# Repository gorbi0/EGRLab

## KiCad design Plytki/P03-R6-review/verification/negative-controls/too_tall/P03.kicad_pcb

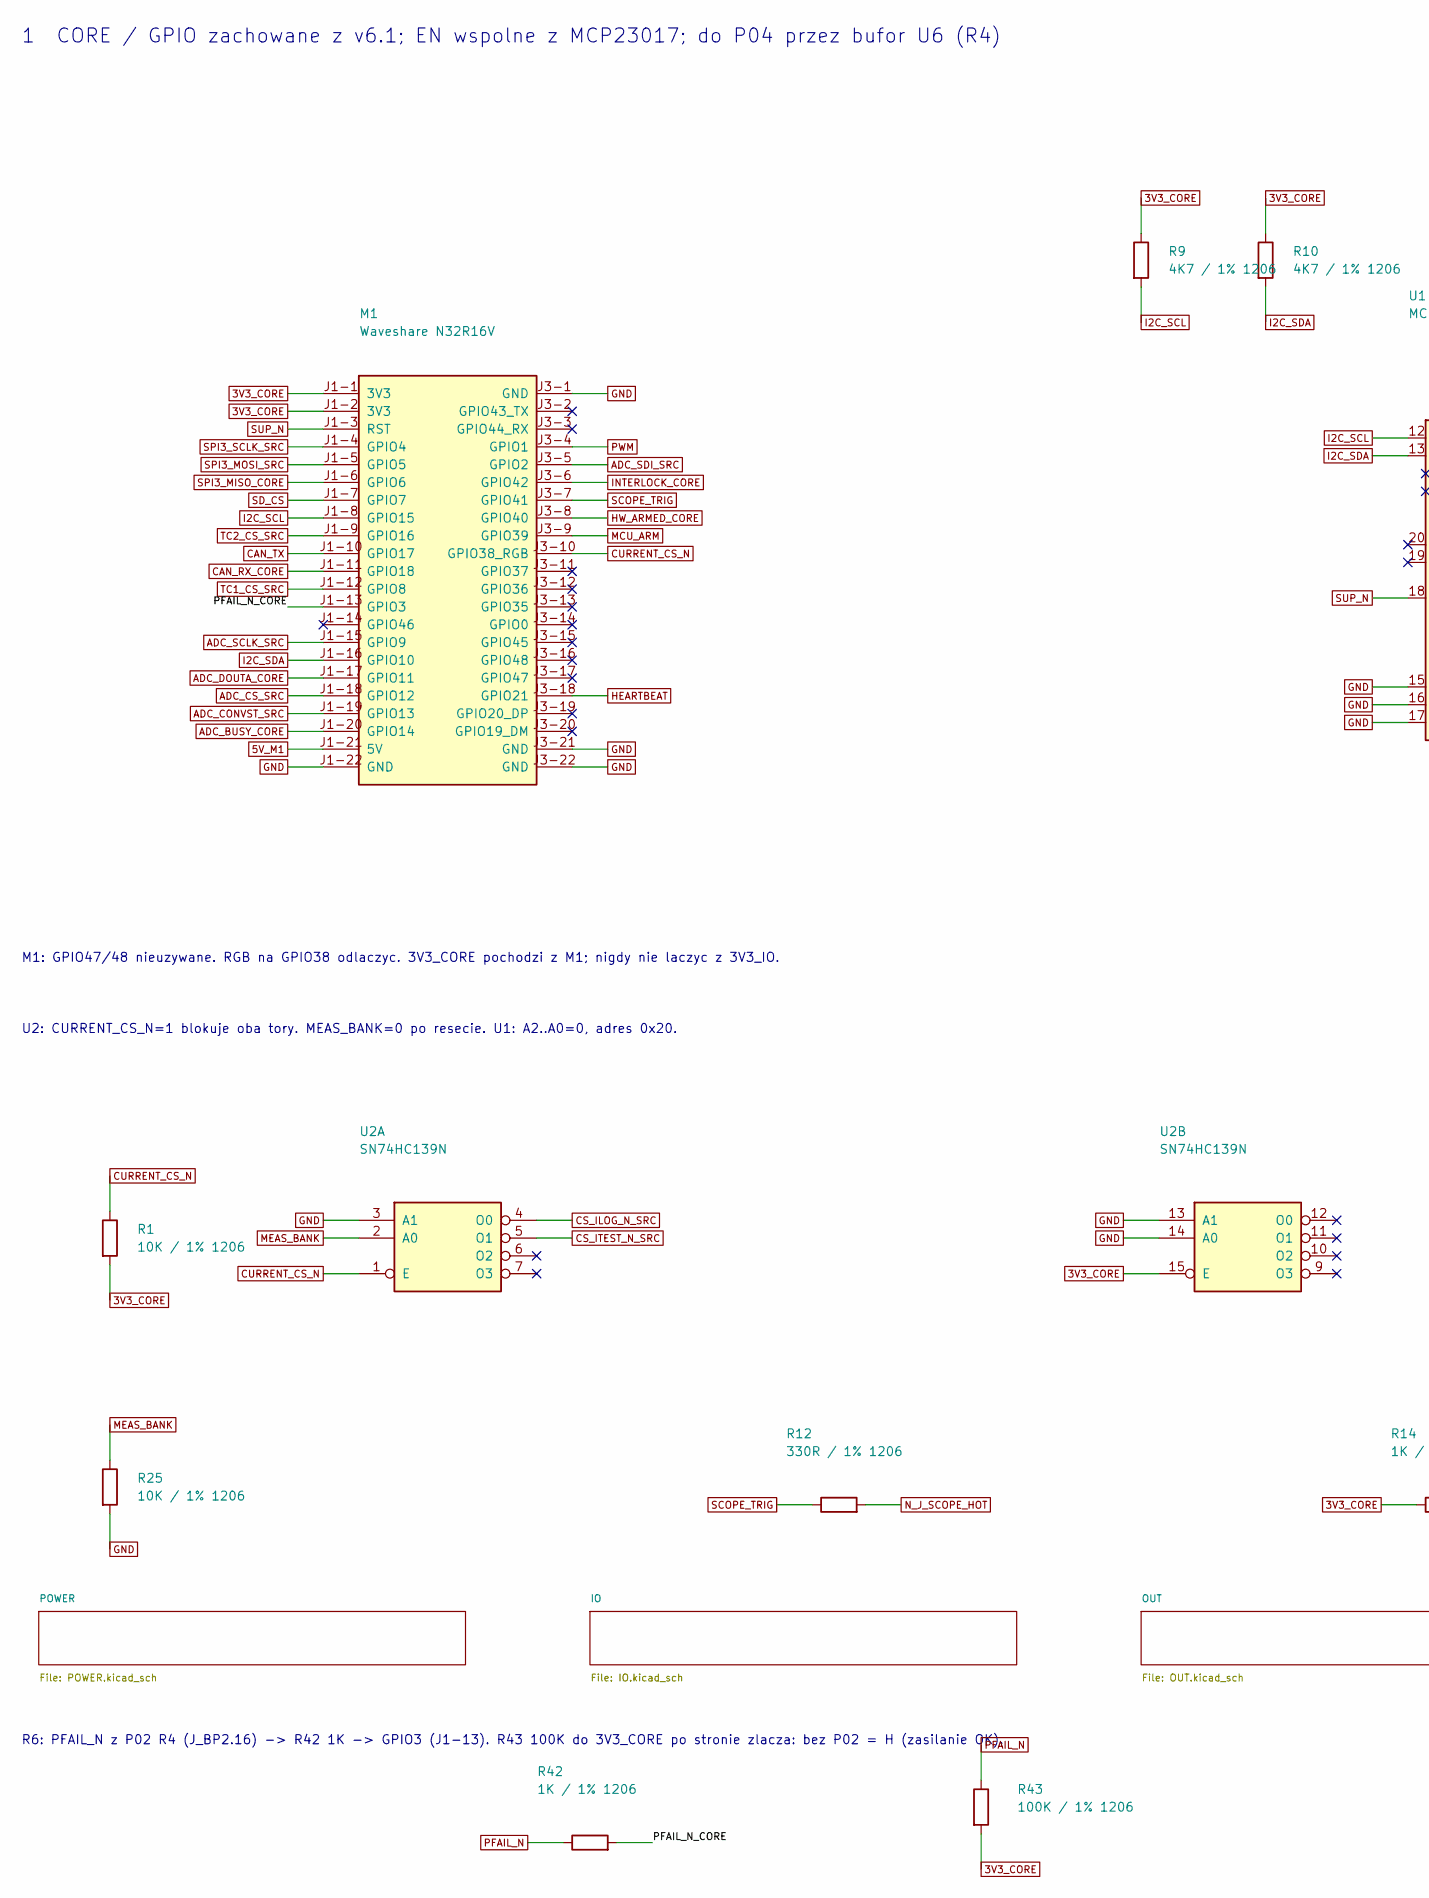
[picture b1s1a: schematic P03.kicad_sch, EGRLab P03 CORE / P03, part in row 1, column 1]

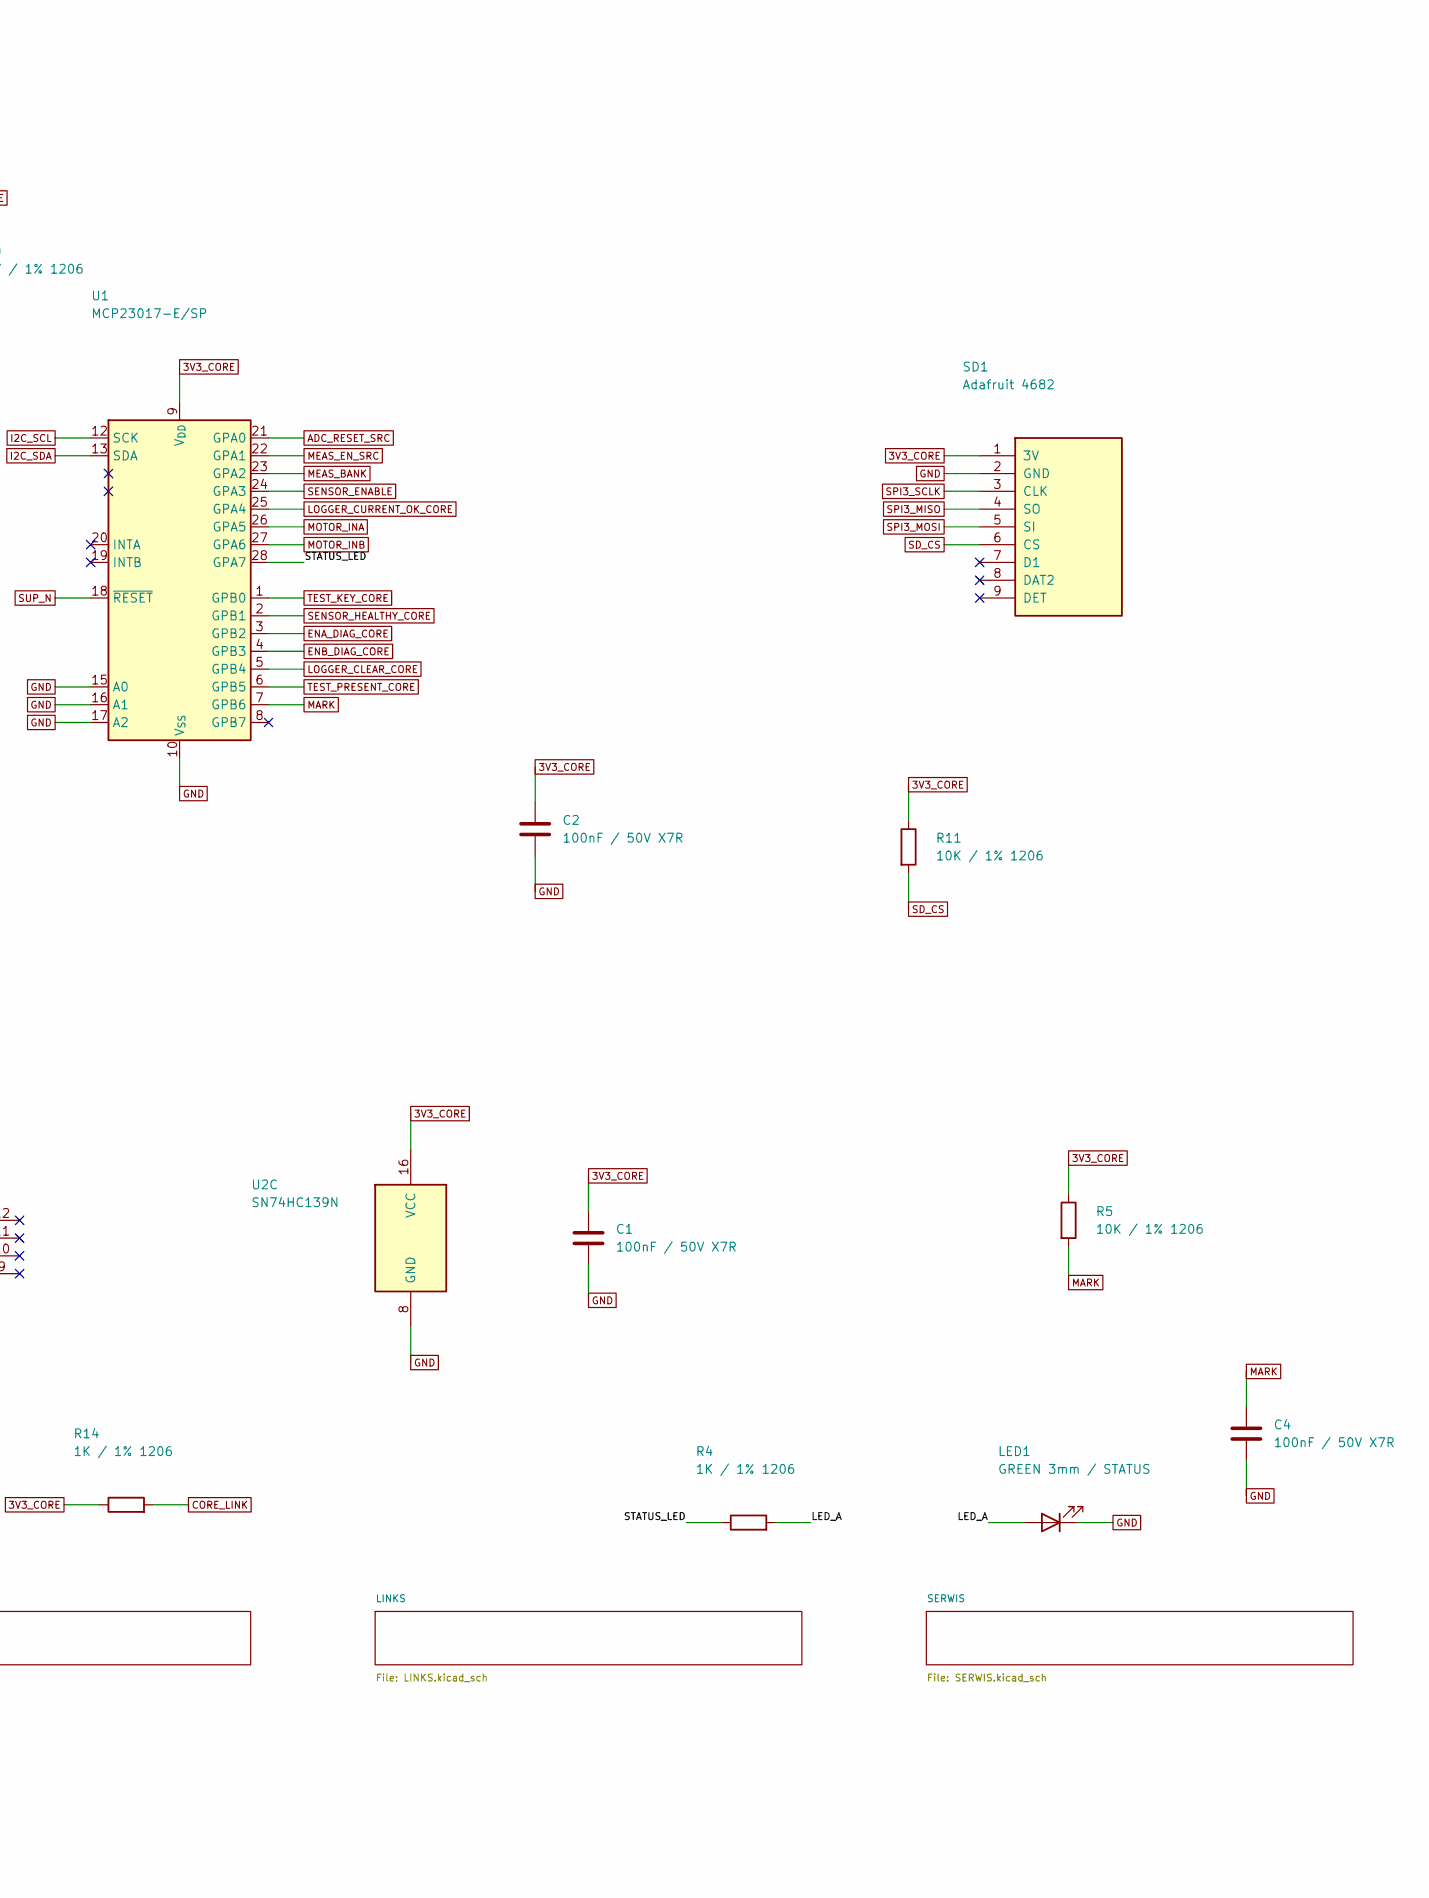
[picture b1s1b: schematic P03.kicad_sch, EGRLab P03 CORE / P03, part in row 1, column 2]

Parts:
C1, C2, C4: 100nF / 50V X7R; C_1206_3216Metric_Pad1.33x1.80mm_HandSolder; MPN GRM31CR71H104KA01L
LED1: GREEN 3mm / STATUS; LED_D3.0mm; MPN L-934GD
M1: Waveshare N32R16V; Waveshare_ESP32-S3-DEV-KIT_2x22_W22.86; MPN owned (Waveshare ESP32-S3-DEV-KIT-N32R1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
R1, R5, R11, R25: 10K / 1% 1206; R_1206_3216Metric_Pad1.30x1.75mm_HandSolder; MPN RC1206FR-0710KL
R4, R14, R42: 1K / 1% 1206; R_1206_3216Metric_Pad1.30x1.75mm_HandSolder; MPN RC1206FR-071KL
R9, R10: 4K7 / 1% 1206; R_1206_3216Metric_Pad1.30x1.75mm_HandSolder; MPN RC1206FR-074K7L
R12: 330R / 1% 1206; R_1206_3216Metric_Pad1.30x1.75mm_HandSolder; MPN RC1206FR-07330RL
R43: 100K / 1% 1206; R_1206_3216Metric_Pad1.30x1.75mm_HandSolder; MPN RC1206FR-07100KL
SD1: Adafruit 4682; Adafruit_4682_microSD_1x09; MPN Adafruit 4682 on a 1x9 female header + 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
U1: MCP23017-E/SP; DIP-28_W7.62mm; MPN MCP23017-E/SP
U2: SN74HC139N; DIP-16_W7.62mm; MPN SN74HC139N

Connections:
5V_M1: M1.J1-21 (5V); also elsewhere on the board
/LED_A: LED1.2 (A), R4.2
/PFAIL_N_CORE: M1.J1-13 (GPIO3), R42.2
/STATUS_LED: R4.1, U1.28 (GPA7)
ADC_BUSY_CORE: M1.J1-20 (GPIO14); also elsewhere on the board
ADC_CONVST_SRC: M1.J1-19 (GPIO13); also elsewhere on the board
ADC_CS_SRC: M1.J1-18 (GPIO12); also elsewhere on the board
ADC_DOUTA_CORE: M1.J1-17 (GPIO11); also elsewhere on the board
ADC_RESET_SRC: U1.21 (GPA0); also elsewhere on the board
ADC_SCLK_SRC: M1.J1-15 (GPIO9); also elsewhere on the board
ADC_SDI_SRC: M1.J3-5 (GPIO2); also elsewhere on the board
CAN_RX_CORE: M1.J1-11 (GPIO18); also elsewhere on the board
CAN_TX: M1.J1-10 (GPIO17); also elsewhere on the board
CORE_LINK: R14.2; also elsewhere on the board
CS_ILOG_N_SRC: U2.4 (O0); also elsewhere on the board
CS_ITEST_N_SRC: U2.5 (O1); also elsewhere on the board
ENA_DIAG_CORE: U1.3 (GPB2); also elsewhere on the board
ENB_DIAG_CORE: U1.4 (GPB3); also elsewhere on the board
GND: C1.2, C2.2, C4.2, LED1.1 (K), M1.J1-22 (GND), M1.J3-1 (GND), M1.J3-21 (GND), M1.J3-22 (GND), R25.2, SD1.2 (GND), U1.10 (V_{SS}), U1.15 (A0), U1.16 (A1), U1.17 (A2), U2.3 (A1), U2.8 (GND), U2.13 (A1), U2.14 (A0); also elsewhere on the board
HEARTBEAT: M1.J3-18 (GPIO21); also elsewhere on the board
HW_ARMED_CORE: M1.J3-8 (GPIO40); also elsewhere on the board
I2C_SDA: M1.J1-16 (GPIO10), R10.2, U1.13 (SDA); also elsewhere on the board
INTERLOCK_CORE: M1.J3-6 (GPIO42); also elsewhere on the board
LOGGER_CLEAR_CORE: U1.5 (GPB4); also elsewhere on the board
LOGGER_CURRENT_OK_CORE: U1.25 (GPA4); also elsewhere on the board
MARK: C4.1, R5.2, U1.7 (GPB6); also elsewhere on the board
MCU_ARM: M1.J3-9 (GPIO39); also elsewhere on the board
MEAS_EN_SRC: U1.22 (GPA1); also elsewhere on the board
MOTOR_INA: U1.26 (GPA5); also elsewhere on the board
MOTOR_INB: U1.27 (GPA6); also elsewhere on the board
N_J_SCOPE_HOT: R12.2; also elsewhere on the board
PWM: M1.J3-4 (GPIO1); also elsewhere on the board
SCOPE_TRIG: M1.J3-7 (GPIO41), R12.1; also elsewhere on the board
SD_CS: M1.J1-7 (GPIO7), R11.2, SD1.6 (CS); also elsewhere on the board
SENSOR_ENABLE: U1.24 (GPA3); also elsewhere on the board
SENSOR_HEALTHY_CORE: U1.2 (GPB1); also elsewhere on the board
SPI3_MISO: SD1.4 (SO); also elsewhere on the board
SPI3_MISO_CORE: M1.J1-6 (GPIO6); also elsewhere on the board
SPI3_MOSI: SD1.5 (SI); also elsewhere on the board
SPI3_MOSI_SRC: M1.J1-5 (GPIO5); also elsewhere on the board
SPI3_SCLK: SD1.3 (CLK); also elsewhere on the board
SPI3_SCLK_SRC: M1.J1-4 (GPIO4); also elsewhere on the board
SUP_N: M1.J1-3 (RST), U1.18 (~RESET); also elsewhere on the board
TC1_CS_SRC: M1.J1-12 (GPIO8); also elsewhere on the board
TC2_CS_SRC: M1.J1-9 (GPIO16); also elsewhere on the board
TEST_KEY_CORE: U1.1 (GPB0); also elsewhere on the board
TEST_PRESENT_CORE: U1.6 (GPB5); also elsewhere on the board

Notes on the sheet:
1 CORE / GPIO zachowane z v6.1; EN wspolne z MCP23017; do P04 przez bufor U6 (R4)
M1: GPIO47/48 nieuzywane. RGB na GPIO38 odlaczyc. 3V3_CORE pochodzi z M1; nigdy nie laczyc z 3V3_IO.
U2: CURRENT_CS_N=1 blokuje oba tory. MEAS_BANK=0 po resecie. U1: A2..A0=0, adres 0x20.
R6: PFAIL_N z P02 R4 (J_BP2.16) -> R42 1K -> GPIO3 (J1-13). R43 100K do 3V3_CORE po stronie zlacza: bez P02 = H (zasilanie OK).

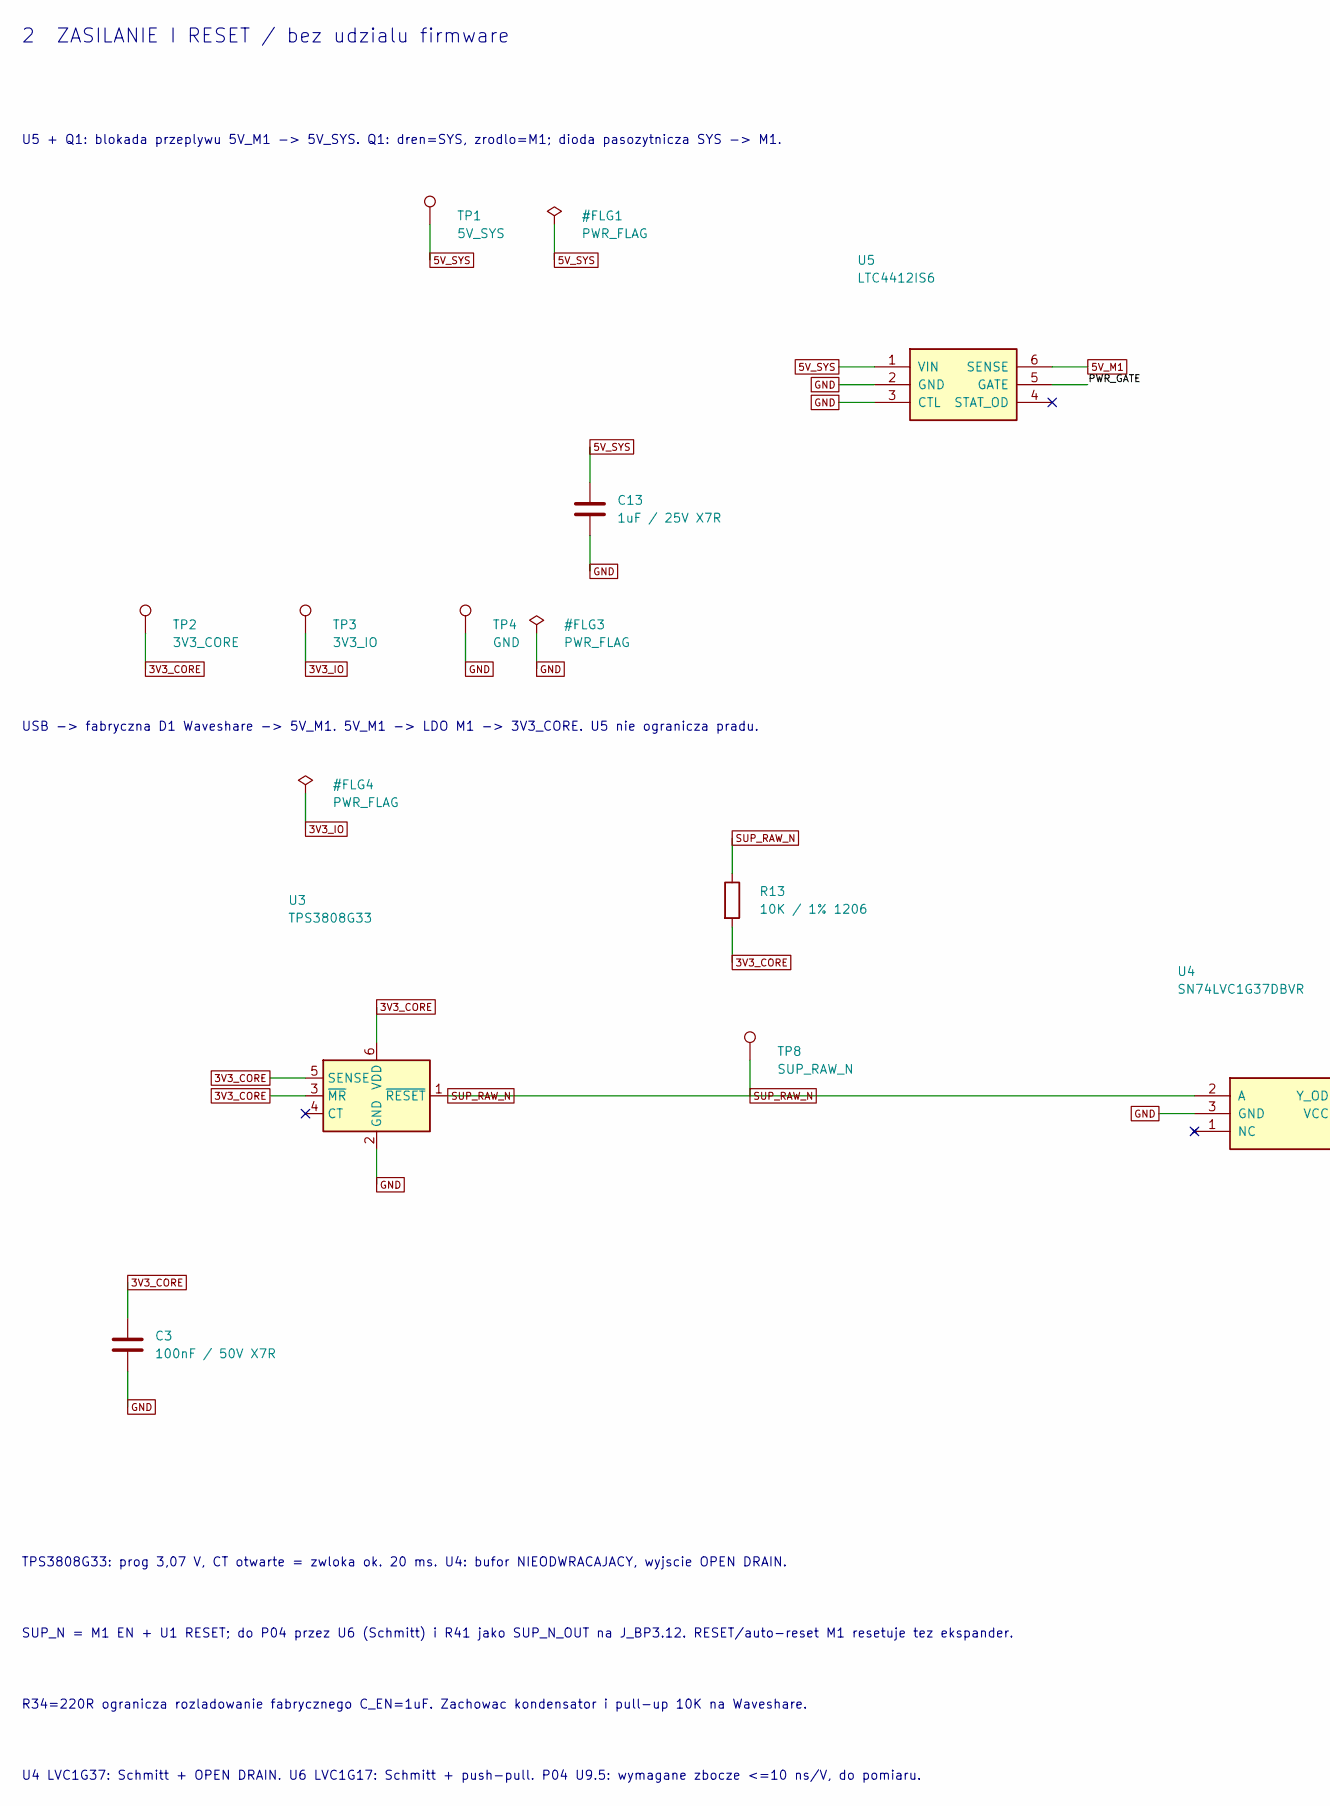
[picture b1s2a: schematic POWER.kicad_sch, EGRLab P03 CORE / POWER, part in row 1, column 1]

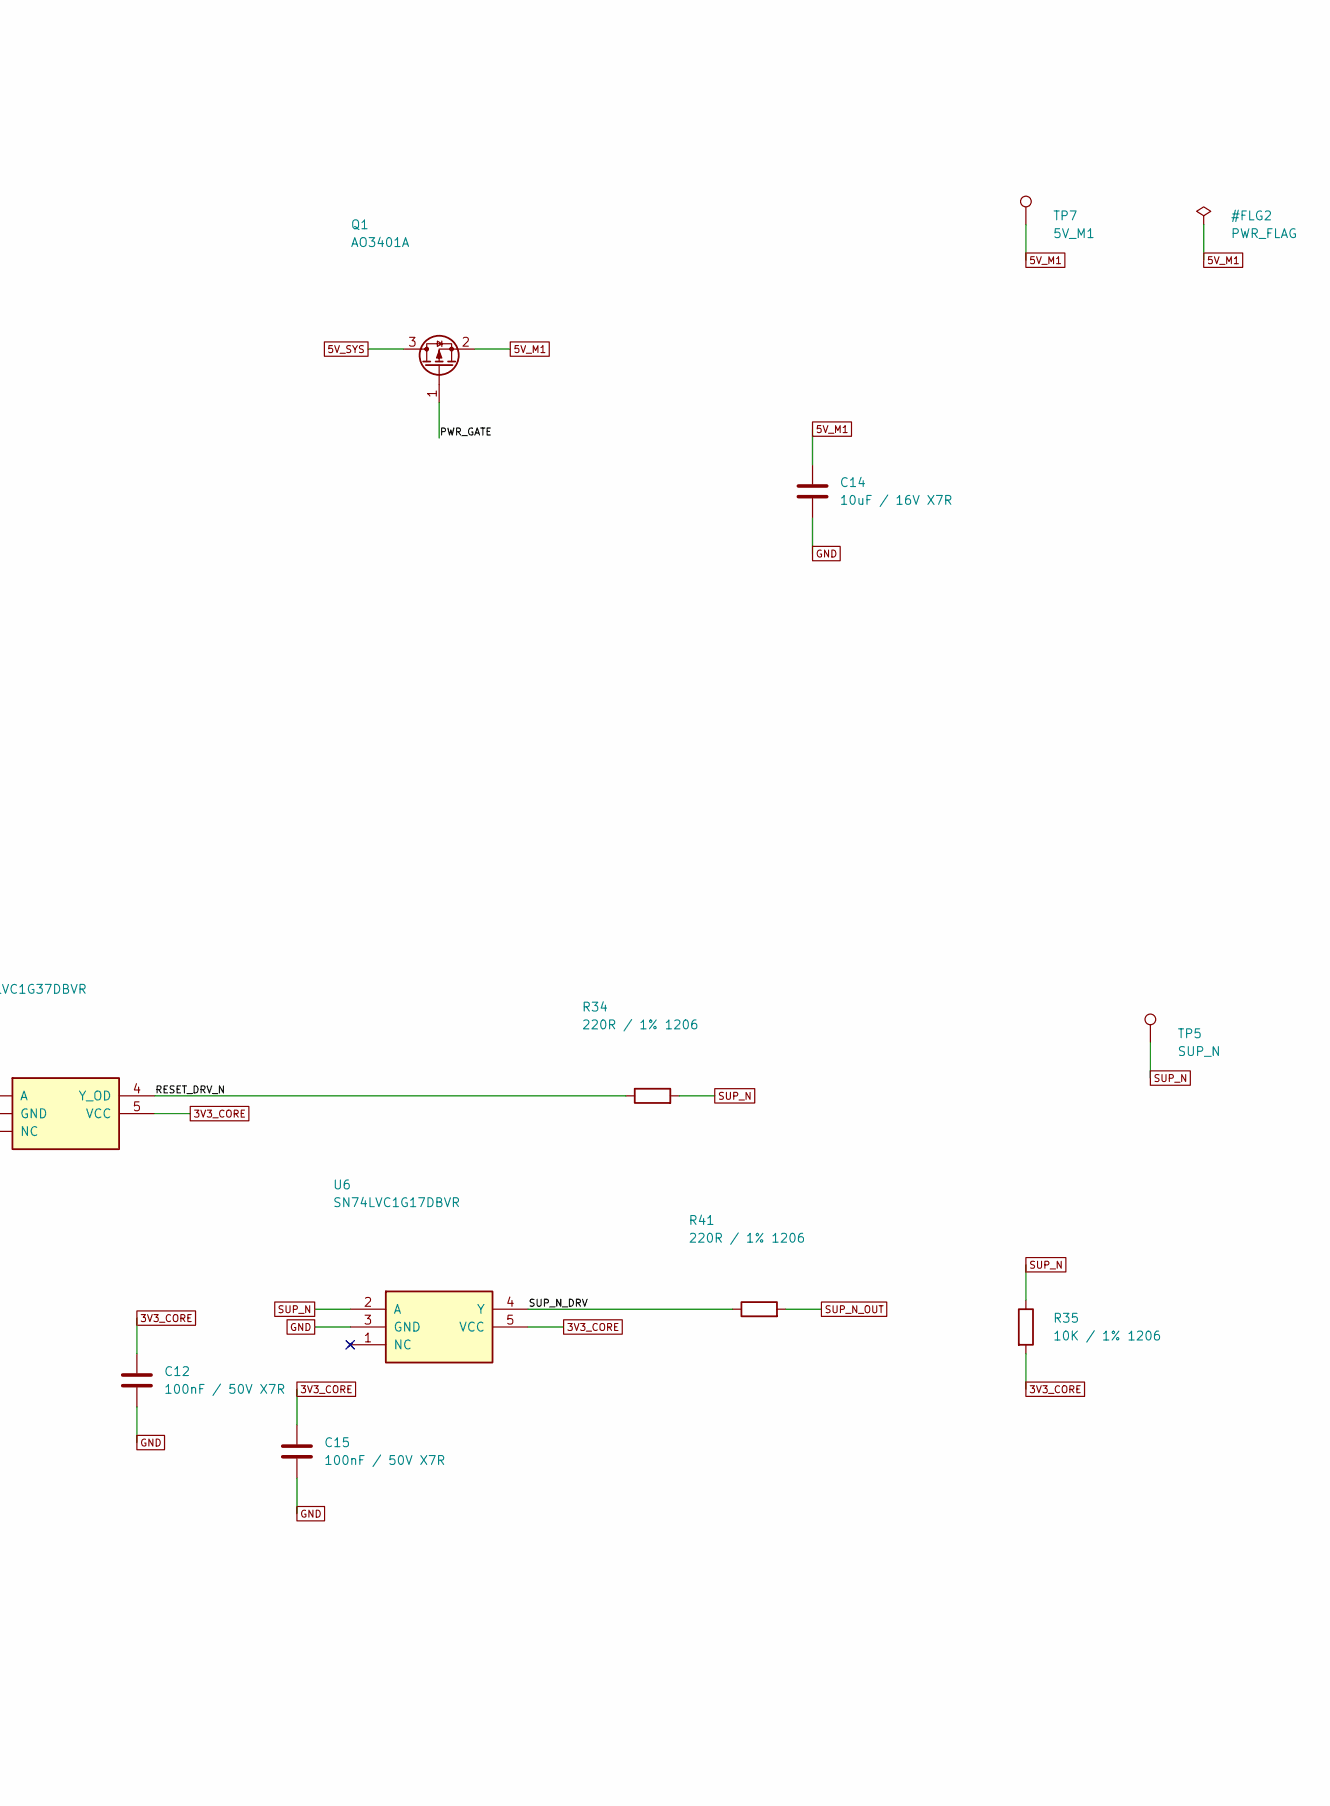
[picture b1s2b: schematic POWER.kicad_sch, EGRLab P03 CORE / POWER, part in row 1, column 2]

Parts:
C3, C12, C15: 100nF / 50V X7R; C_1206_3216Metric_Pad1.33x1.80mm_HandSolder; MPN GRM31CR71H104KA01L
C13: 1uF / 25V X7R; C_1206_3216Metric_Pad1.33x1.80mm_HandSolder; MPN GRM31CR71E105KA12L
C14: 10uF / 16V X7R; C_1206_3216Metric_Pad1.33x1.80mm_HandSolder; MPN GRM31CR71C106KA12L
Q1: AO3401A; SOT-23; MPN AO3401A
R13, R35: 10K / 1% 1206; R_1206_3216Metric_Pad1.30x1.75mm_HandSolder; MPN RC1206FR-0710KL
R34, R41: 220R / 1% 1206; R_1206_3216Metric_Pad1.30x1.75mm_HandSolder; MPN RC1206FR-07220RL
TP1: 5V_SYS; TestPad_1; MPN PCB test pad
TP2: 3V3_CORE; TestPad_1; MPN PCB test pad
TP3: 3V3_IO; TestPad_1; MPN PCB test pad
TP4: GND; TestPad_1; MPN PCB test pad
TP5: SUP_N; TestPad_1; MPN PCB test pad
TP7: 5V_M1; TestPad_1; MPN PCB test pad
TP8: SUP_RAW_N; TestPad_1; MPN PCB test pad
U3: TPS3808G33; SOT-23-6; MPN TPS3808G33DBVR
U4: SN74LVC1G37DBVR; SOT-23-5; MPN SN74LVC1G37DBVR
U5: LTC4412IS6; SOT-23-6; MPN LTC4412IS6#TRPBF
U6: SN74LVC1G17DBVR; SOT-23-5; MPN SN74LVC1G17DBVR

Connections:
3V3_IO: TP3.1; also elsewhere on the board
5V_M1: C14.1, Q1.2 (S), TP7.1, U5.6 (SENSE); also elsewhere on the board
5V_SYS: C13.1, Q1.3 (D), TP1.1, U5.1 (VIN); also elsewhere on the board
/POWER/PWR_GATE: Q1.1 (G), U5.5 (GATE)
/POWER/RESET_DRV_N: R34.1, U4.4 (Y_OD)
/POWER/SUP_N_DRV: R41.1, U6.4 (Y)
GND: C3.2, C12.2, C13.2, C14.2, C15.2, TP4.1, U3.2 (GND), U4.3 (GND), U5.2 (GND), U5.3 (CTL), U6.3 (GND); also elsewhere on the board
SUP_N: R34.2, R35.1, TP5.1, U6.2 (A); also elsewhere on the board
SUP_N_OUT: R41.2; also elsewhere on the board
SUP_RAW_N: R13.1, TP8.1, U3.1 (~RESET), U4.2 (A); also elsewhere on the board

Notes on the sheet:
2 ZASILANIE I RESET / bez udzialu firmware
U5 + Q1: blokada przeplywu 5V_M1 -> 5V_SYS. Q1: dren=SYS, zrodlo=M1; dioda pasozytnicza SYS -> M1.
USB -> fabryczna D1 Waveshare -> 5V_M1. 5V_M1 -> LDO M1 -> 3V3_CORE. U5 nie ogranicza pradu.
TPS3808G33: prog 3,07 V, CT otwarte = zwloka ok. 20 ms. U4: bufor NIEODWRACAJACY, wyjscie OPEN DRAIN.
SUP_N = M1 EN + U1 RESET; do P04 przez U6 (Schmitt) i R41 jako SUP_N_OUT na J_BP3.12. RESET/auto-reset M1 resetuje tez ekspander.
R34=220R ogranicza rozladowanie fabrycznego C_EN=1uF. Zachowac kondensator i pull-up 10K na Waveshare.
U4 LVC1G37: Schmitt + OPEN DRAIN. U6 LVC1G17: Schmitt + push-pull. P04 U9.5: wymagane zbocze <=10 ns/V, do pomiaru.

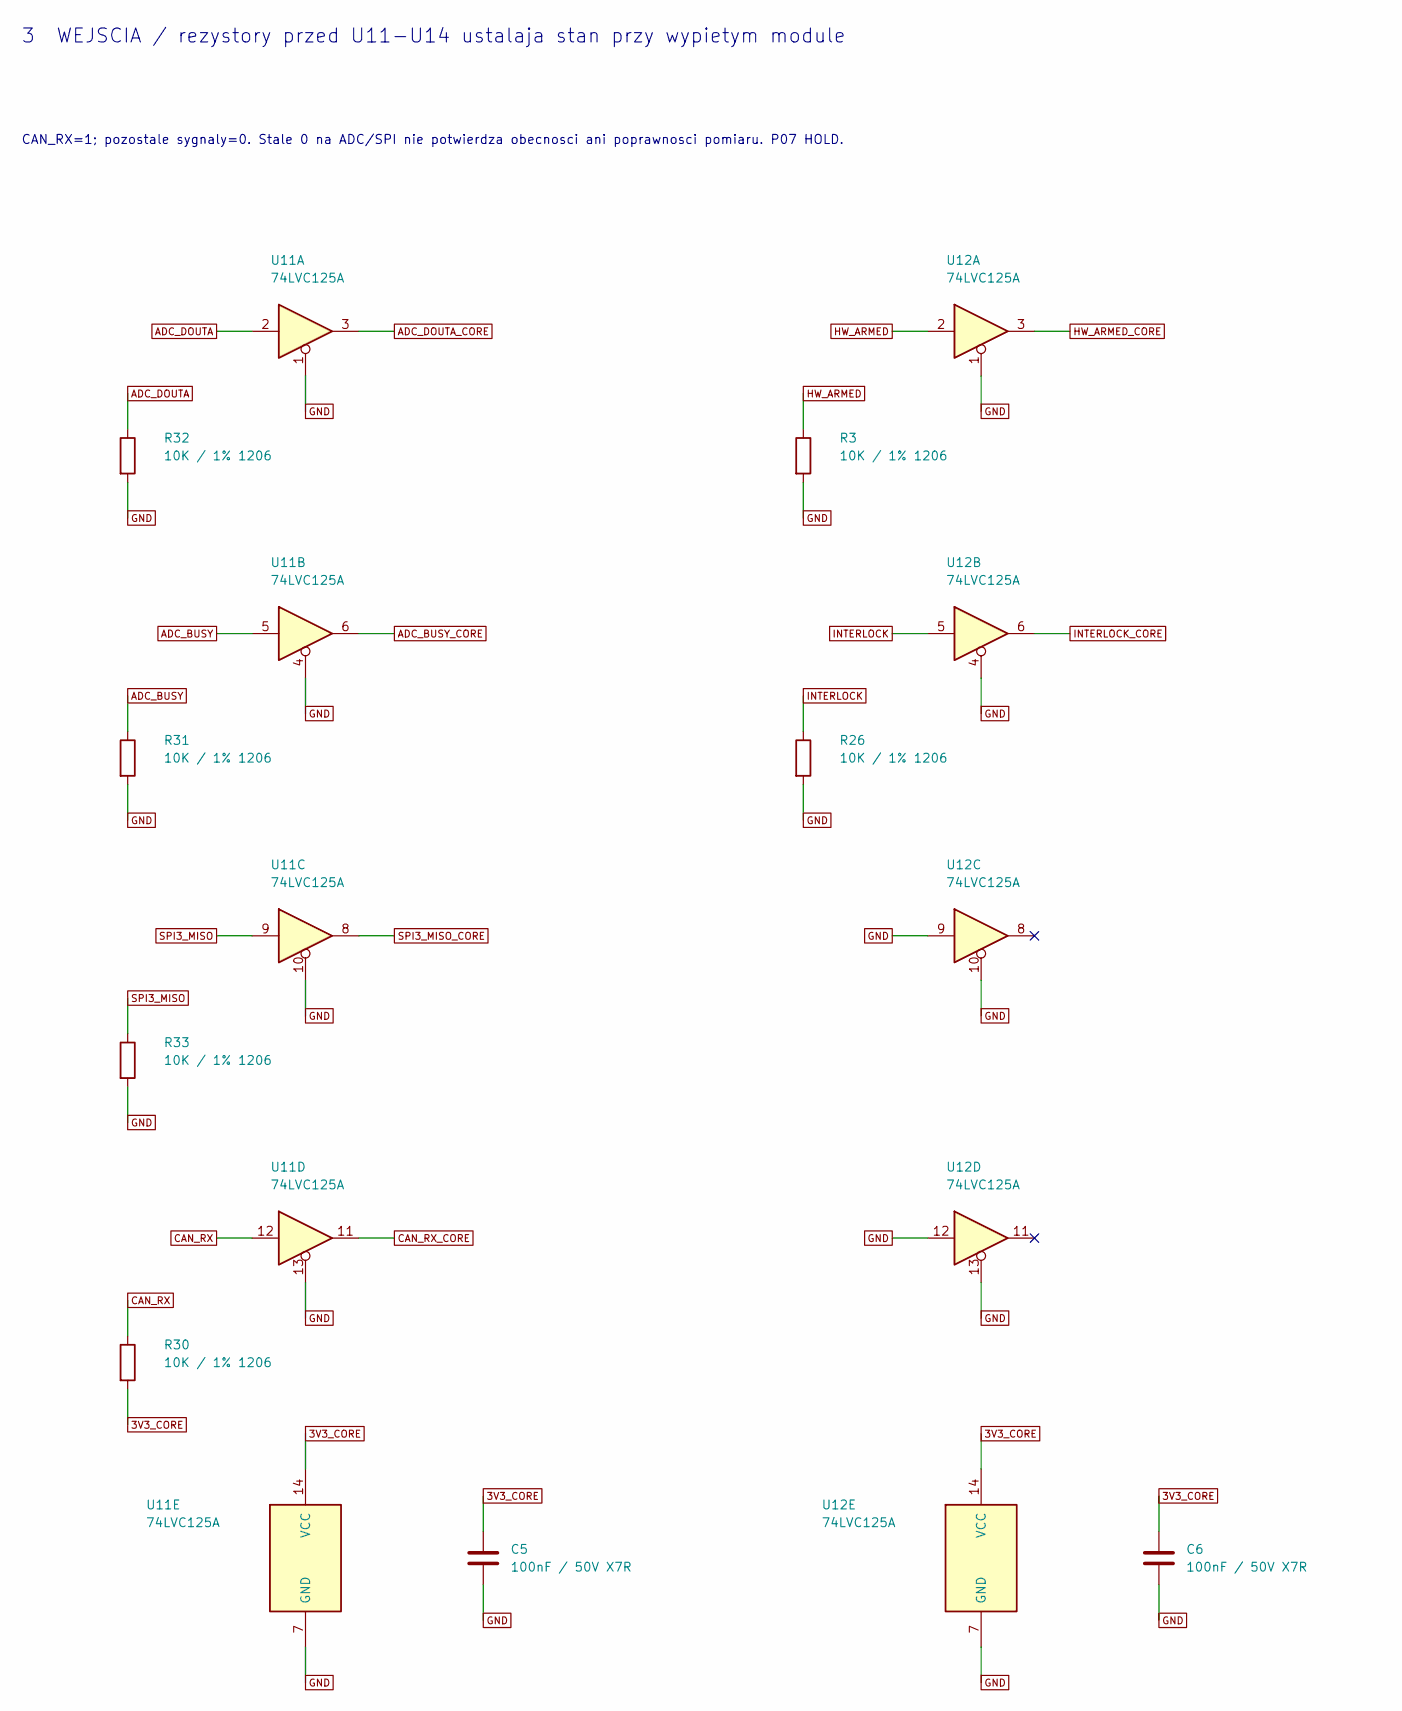
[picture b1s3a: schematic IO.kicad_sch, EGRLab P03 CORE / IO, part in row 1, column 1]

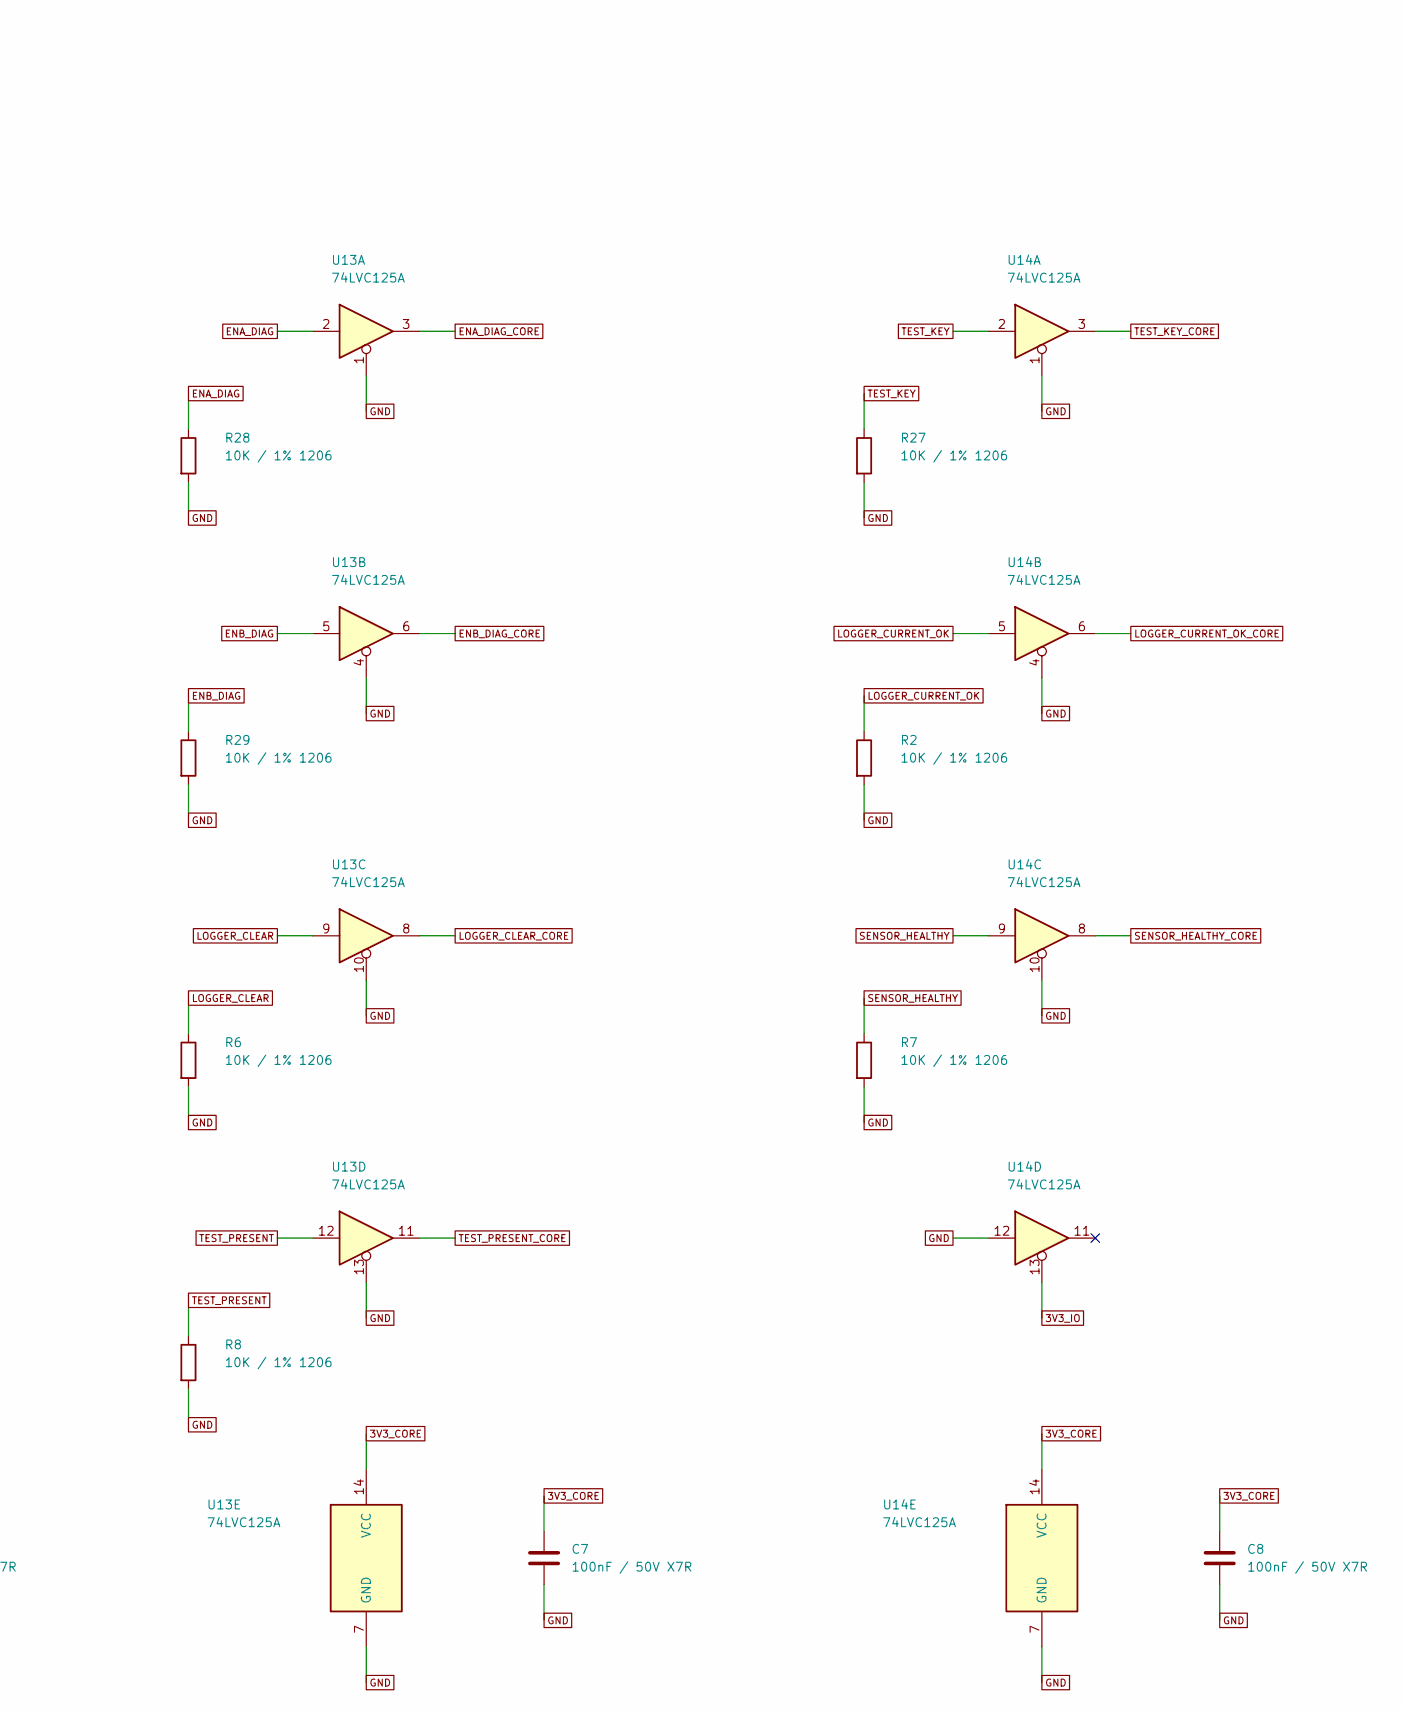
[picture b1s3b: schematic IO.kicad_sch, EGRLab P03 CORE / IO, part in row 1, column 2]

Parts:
C5, C6, C7, C8: 100nF / 50V X7R; C_1206_3216Metric_Pad1.33x1.80mm_HandSolder; MPN GRM31CR71H104KA01L
R2, R3, R6, R7, R8, R26, R27, R28, R29, R30, R31, R32, R33: 10K / 1% 1206; R_1206_3216Metric_Pad1.30x1.75mm_HandSolder; MPN RC1206FR-0710KL
U11, U12, U13, U14: 74LVC125A; SOIC-14_3.9x8.7mm_P1.27mm; MPN 74LVC125AD,118 (Nexperia)

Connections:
3V3_IO: U14.13; also elsewhere on the board
ADC_BUSY: R31.1, U11.5; also elsewhere on the board
ADC_BUSY_CORE: U11.6; also elsewhere on the board
ADC_DOUTA: R32.1, U11.2; also elsewhere on the board
ADC_DOUTA_CORE: U11.3; also elsewhere on the board
CAN_RX: R30.1, U11.12; also elsewhere on the board
CAN_RX_CORE: U11.11; also elsewhere on the board
ENA_DIAG: R28.1, U13.2; also elsewhere on the board
ENA_DIAG_CORE: U13.3; also elsewhere on the board
ENB_DIAG: R29.1, U13.5; also elsewhere on the board
ENB_DIAG_CORE: U13.6; also elsewhere on the board
GND: C5.2, C6.2, C7.2, C8.2, R2.2, R3.2, R6.2, R7.2, R8.2, R26.2, R27.2, R28.2, R29.2, R31.2, R32.2, R33.2, U11.1, U11.4, U11.7 (GND), U11.10, U11.13, U12.1, U12.4, U12.7 (GND), U12.9, U12.10, U12.12, U12.13, U13.1, U13.4, U13.7 (GND), U13.10, U13.13, U14.1, U14.4, U14.7 (GND), U14.10, U14.12; also elsewhere on the board
HW_ARMED: R3.1, U12.2; also elsewhere on the board
HW_ARMED_CORE: U12.3; also elsewhere on the board
INTERLOCK: R26.1, U12.5; also elsewhere on the board
INTERLOCK_CORE: U12.6; also elsewhere on the board
LOGGER_CLEAR: R6.1, U13.9; also elsewhere on the board
LOGGER_CLEAR_CORE: U13.8; also elsewhere on the board
LOGGER_CURRENT_OK_CORE: U14.6; also elsewhere on the board
SENSOR_HEALTHY: R7.1, U14.9; also elsewhere on the board
SENSOR_HEALTHY_CORE: U14.8; also elsewhere on the board
SPI3_MISO: R33.1, U11.9; also elsewhere on the board
SPI3_MISO_CORE: U11.8; also elsewhere on the board
TEST_KEY: R27.1, U14.2; also elsewhere on the board
TEST_KEY_CORE: U14.3; also elsewhere on the board
TEST_PRESENT: R8.1, U13.12; also elsewhere on the board
TEST_PRESENT_CORE: U13.11; also elsewhere on the board

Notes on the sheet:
3 WEJSCIA / rezystory przed U11-U14 ustalaja stan przy wypietym module
CAN_RX=1; pozostale sygnaly=0. Stale 0 na ADC/SPI nie potwierdza obecnosci ani poprawnosci pomiaru. P07 HOLD.
